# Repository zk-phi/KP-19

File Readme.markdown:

# KP-19

遊舎工房 meishi 展に合わせて作成した、実験要素モリモリの 4 キーキーボードです。

メディアキー（音量、再生/停止など）として使うことを想定しています。

- 音楽に同期した LED イルミネーション
  - おそらく初めて SK6812Side LED を採用したキーボード基板
  - 19 は最大 LED 数です

- キーを押した時のハプティック（触覚）フィードバック
  - リニアスイッチにタクタイル感を後付けしたい！的な

動画あります：

<blockquote class="twitter-tweet" data-lang="ja"><p lang="ja" dir="ltr">meishiキーボードもといイルミネーションです！！！ <a href="https://t.co/v1jvpHVXxa">pic.twitter.com/v1jvpHVXxa</a></p>&mdash; ぜろけー🔨 (@zk_phi) <a href="https://twitter.com/zk_phi/status/1127585762080256000?ref_src=twsrc%5Etfw">2019年5月12日</a></blockquote>

----

販売予定はいまのところありません。 meishi 展にて「meishi 交換」を受け付ける予定です。

まだまだ詰めなければいけない箇所が多いので、「わかる人向け」です。

## 遊び方

二つある TRRS ジャックの片方に音楽プレーヤーを、他方にイヤホンやスピーカーを繋ぐと、楽しいです。

精度よく光らせるためには、音楽プレーヤーの音量をかなり上げる必要があります (アンプとか内蔵した方が便利だよな…とは思っています)。

## 実装例

表

裏

## 組立
### 部品表

基板の他に：

- キーボードとして必須
  - MX 互換スイッチ x 4
  - リセットスイッチ TVBP06 x 1
  - Pro Micro x 1
  - ゴム足 (裏面につける部品より厚いもの) x 4 など

- LED (オプション)
  1. Backlight 用 SK6812MINI x 4
  2. Underglow 用 SK6812MINI x 5
  3. 表面でキースイッチを照らす SK6812SIDE x 10
  - 1 -> 2 -> 3 の順で直列に繋がっているので、1 のみ、1 と 2 のみも可能

- 音声入出力 (オプション)
  - TRRS ジャック MJ4-PP-9 x 2
  - コンデンサ x 1 ... 2.5mm ピッチの積層セラミックコンデンサを想定
  - 同じ値の抵抗 x 2 ... 1/6W サイズのカーボン抵抗を想定
  - フットプリントには 10uF, 100K と書いてありますが、のちにいろいろ試して 1uF, 47K の方が多少安定しました
    - アナログ回路ぜんぜんわからないので誰か教えてください…

- 振動モータ (オプション)
  - トランジスタ 2SC1815 x 1
  - 整流用ダイオード 1N4007 x 1
  - 振動モーター x 1 (秋月の円盤型振動モーターなど。直流でそのまま駆動できるもの)

### 手順

0. Pro Micro にファームを焼いて、コンスルーをつけておく

https://github.com/zk-phi/qmk_firmware

: make handwired/kp_19:default:avrdude

1. 失敗しやすいので LED をまずつける (Pro Micro を刺して光ることを確認しながら)

SK6812Side は半田付けがかなり難しいです。フラックスを塗って、１ピンだけ予備半田して仮止めしてから、残りのパッドに半田を流す、とするとうまくいきました。 SK6812MINI と同様に熱に弱いので注意してください。

また、ピンの間隔が狭いので、隣のピンにズレてつけてしまったりしないように気をつけてください。ルーペなどで確認しながら進めると快適でした。

2. 残りのリード部品を背の低い順につける
3. 振動モーターを両面テープなどで貼り付けて、裏面のパッドに配線
4. ゴム足を貼って完成

## 課題s

誰か強い人に頑張ってほしいポイントたち

### 振動モーターが微妙

基板にベタッと貼っただけではあまり指に刺激がありませんでした。

長めにブイーと駆動すれば振動は強くなりますが、それはそれでキレがなくなり「タクタイル感」とは程遠いです。

スイッチのステムがバネで基板から浮いているので、そりゃ振動伝わりにくいよねという説が濃厚です。

### アナログ回路が発振する

LED をバチバチ光らせながらイヤホンやスピーカーをつなぐと、うっすら「ピー」という音がずっと聞こえます。

LED をオフにしたり、逆に輝度 MAX にしたりすると鳴らないので、 Neopixel 内部の PWM 制御かなにかが出すノイズを拾ってしまっているんじゃないかと思います。

基板のノイズ対策不足、パスコンがない、カップリングの定数決めがよくない、などがあるかなと思っているんですが、アナログ回路全然わからないので誰か教えてほしいです。

そもそもアンプをつけて S/N を改善したいという話もあります。

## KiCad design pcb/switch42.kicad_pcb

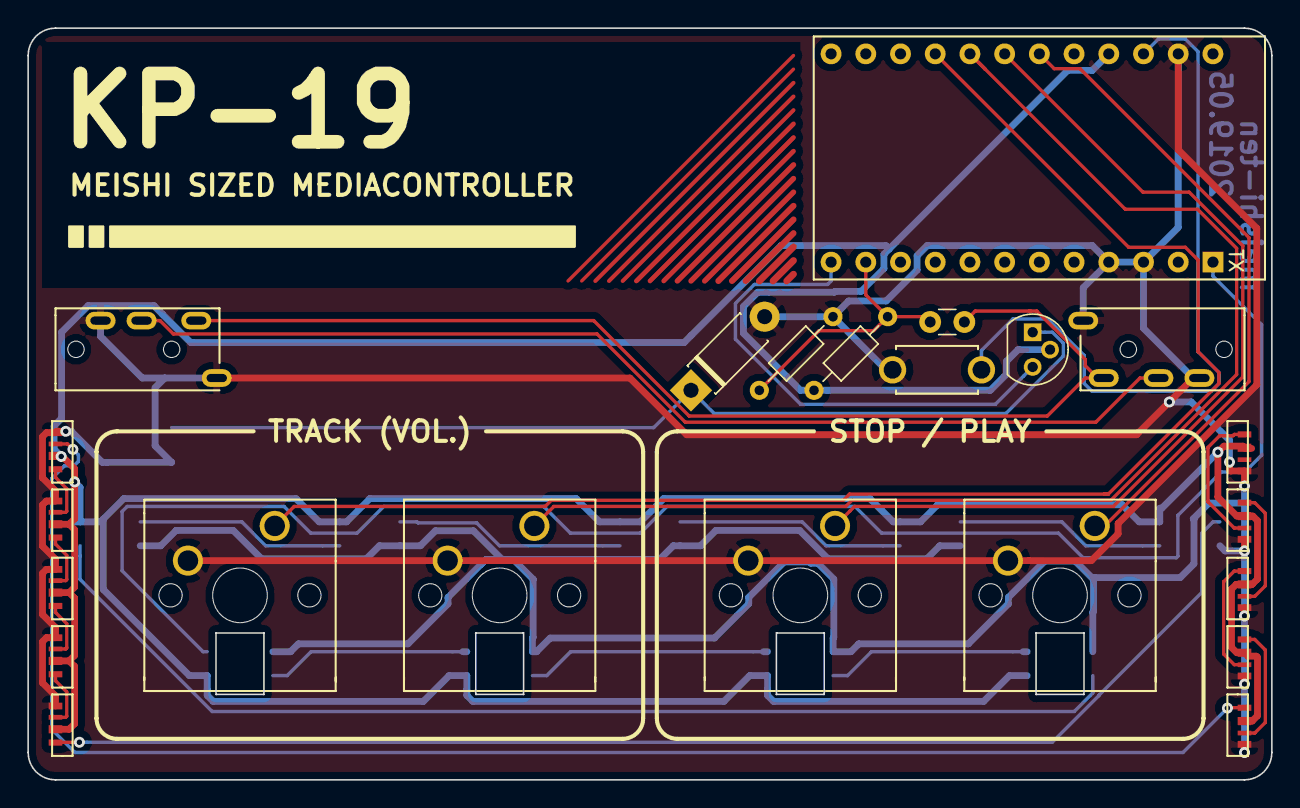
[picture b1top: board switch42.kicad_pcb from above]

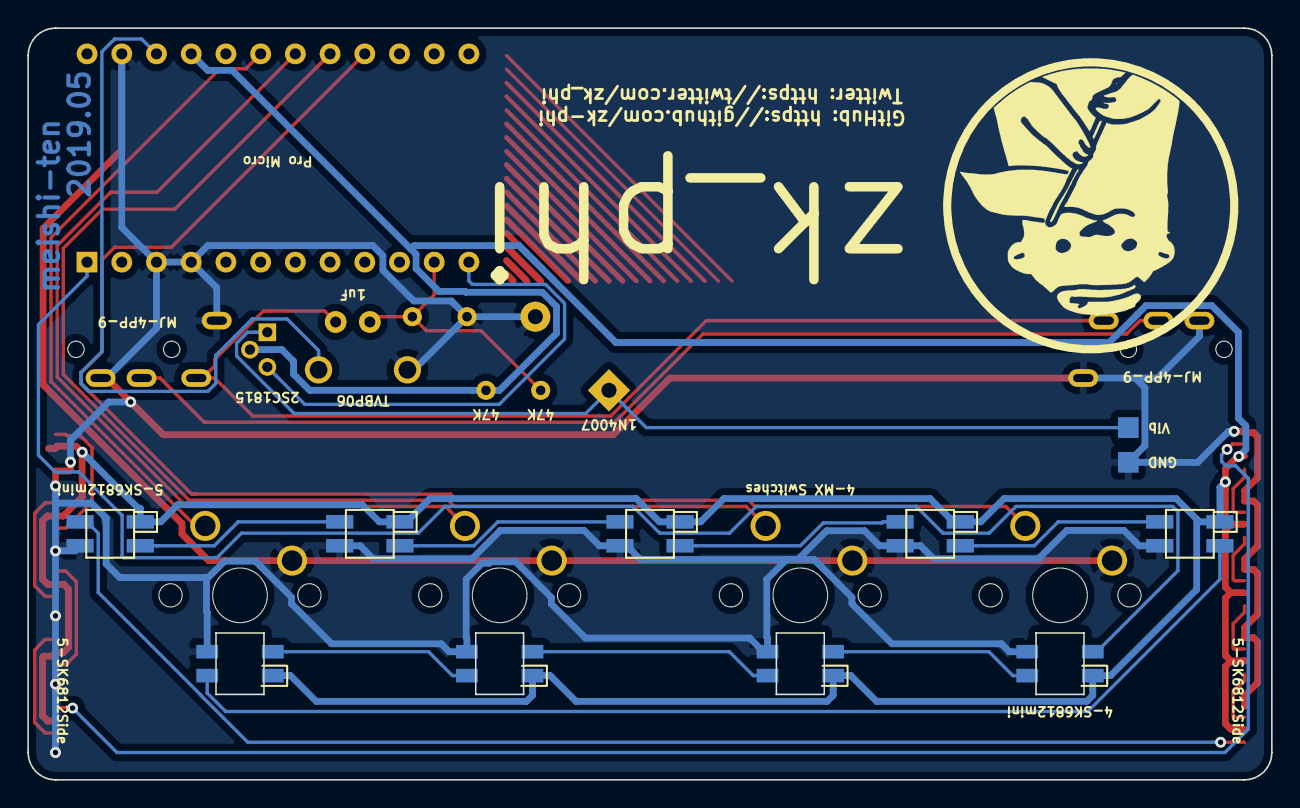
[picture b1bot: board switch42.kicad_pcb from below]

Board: 2 copper layers, 91.0 x 55.0 mm, 33 parts (10 on the bottom side), 31 nets.

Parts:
C1: C; C_Disc_D3.0mm_W1.6mm_P2.50mm
D1: D; D_DO-41_SOD81_P7.62mm_Horizontal
J1: Conn_01x02; 2pads
J2, J3: MJ-4PP-9; MJ-4PP-9-irreversible
L1, L3, L5, L7, L9: SK6812MINI; SK6812MINI-underglow-irreversible
L2, L4, L6, L8, L10, L11, L12, L13, L14, L15: SK6812MINI; SK6812SIDE-irreversible
L16, L17, L18, L19: SK6812MINI; SK6812MINI-irreversible
Q1: Q_NPN_ECB; TO-92
R1, R2: R; R_Axial_DIN0204_L3.6mm_D1.6mm_P7.62mm_Horizontal
SW1, SW2, SW4, SW5: SW_PUSH; MX_1.00u-irreversible
SW7: SW_PUSH; ResetSW-irreversible
U1: ProMicro; ProMicro_Reversed_Conthrough-irreversible

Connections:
GND: D1.2, J1.2, J2.A, J2.B, J3.A, J3.B, L1.2, L2.2, L3.2, L4.2, L5.2, L6.2, L7.2, L8.2, L9.2, L10.2, L11.2, L12.2, L13.2, L14.2, L15.2, L16.2, L17.2, L18.2, L19.2, R2.2, SW1.1, SW2.1, SW4.1, SW5.1, SW7.2, U1.3, U1.4, U1.23
unnamed: C1.2, J2.D, J3.D
unnamed: D1.1, J1.1, Q1.1
unnamed: J2.C, J3.C
unnamed: L1.1, L3.3
unnamed: L2.1, L4.3
unnamed: L3.1, L5.3
unnamed: L4.1, L6.3
unnamed: L5.1, L7.3
unnamed: L6.1, L8.3
unnamed: L7.1, L9.3
unnamed: L10.1, L11.3
unnamed: L8.1, L10.3
unnamed: L11.1, L12.3
unnamed: L12.1, L13.3
unnamed: L13.1, L14.3
unnamed: L14.1, L15.3
unnamed: L16.1, L17.3
unnamed: L17.1, L18.3
unnamed: L18.1, L19.3
VCC: L1.4, L2.4, L3.4, L4.4, L5.4, L6.4, L7.4, L8.4, L9.4, L10.4, L11.4, L12.4, L13.4, L14.4, L15.4, L16.4, L17.4, L18.4, L19.4, Q1.2, R1.1, U1.21
audio: C1.1, R1.2, R2.1, U1.11
backlight: L16.3, U1.1
led: L2.3, L9.1
reset: SW7.1, U1.22
sw1: SW1.2, U1.16
sw2: SW4.2, U1.17
sw3: SW2.2, U1.18
sw4: SW5.2, U1.19
underglow: L1.3, L19.1
vib: Q1.3, U1.12

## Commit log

2019-04-23 Copy-pasted pcb from switch42
2019-04-28 KP-19 pcb
2019-04-29 FIx resistor values
2019-04-29 Use two-colored logo
2019-05-02 Swap silk and mask of the icon
2019-05-02 Subtract mask from silk
2019-05-09 Tweak name size and position
2019-05-13 Change register and capacitor values
2019-05-13 Update SK6812Side footprint
2019-05-13 Add Readme.markdown
2019-05-13 Add LICENSE
2019-05-13 Fix LICENSE
